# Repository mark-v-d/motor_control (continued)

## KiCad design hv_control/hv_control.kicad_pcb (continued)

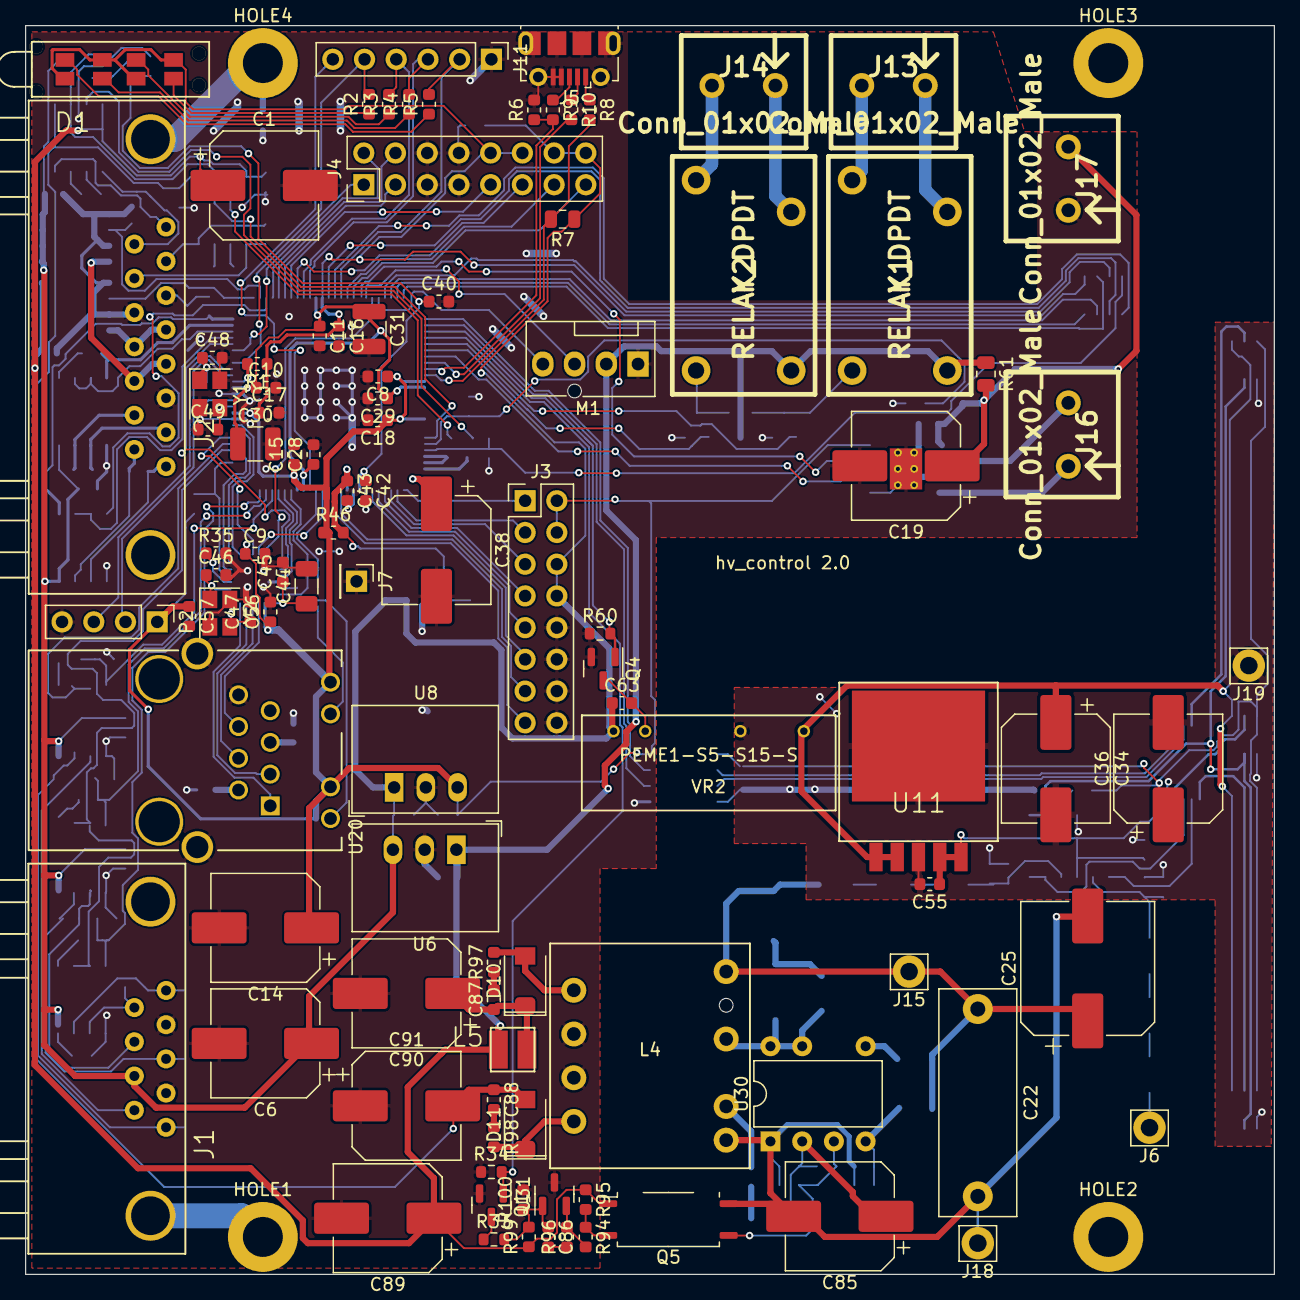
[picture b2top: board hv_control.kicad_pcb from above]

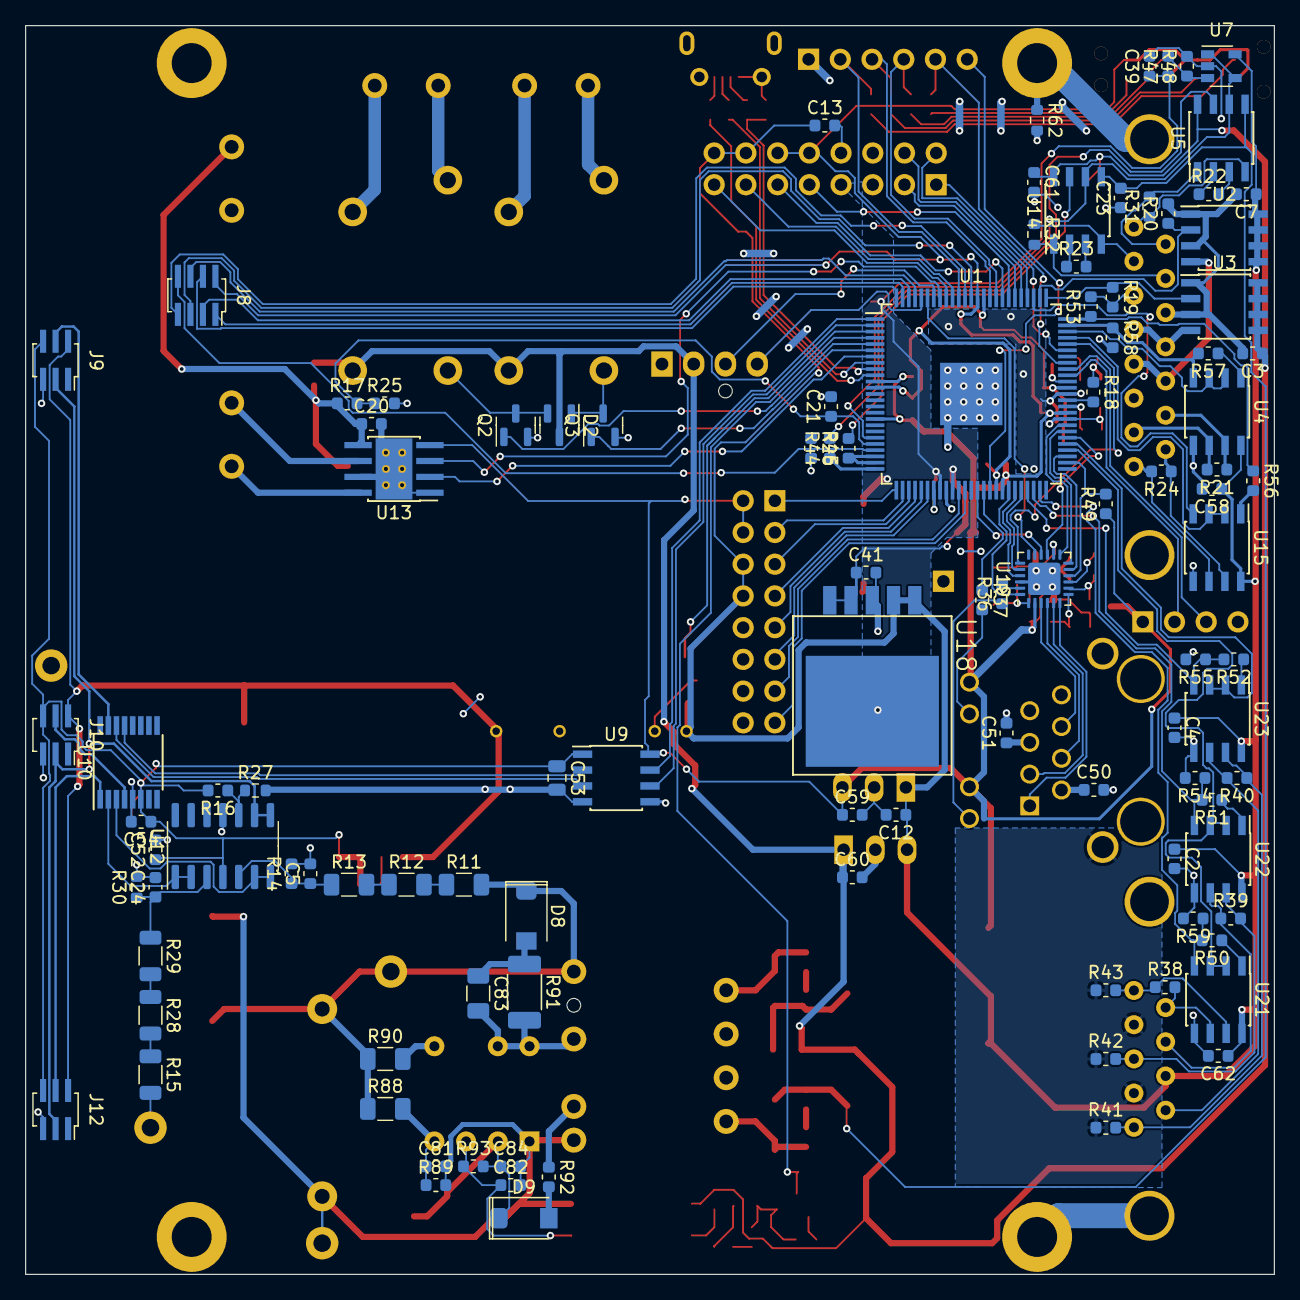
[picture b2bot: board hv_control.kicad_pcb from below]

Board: 2 copper layers, 100.0 x 100.0 mm, 209 parts (105 on the bottom side), 180 nets.

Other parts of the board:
C25: 4.7uF; CP_Elec_10x14.3
Q5: TCLT1003; SOP-4_3.8x7.5mm_P2.54mm

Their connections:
+800V: C25.1; also elsewhere on the board
GNDPWR: C25.2, Q5.4 (E); also elsewhere on the board

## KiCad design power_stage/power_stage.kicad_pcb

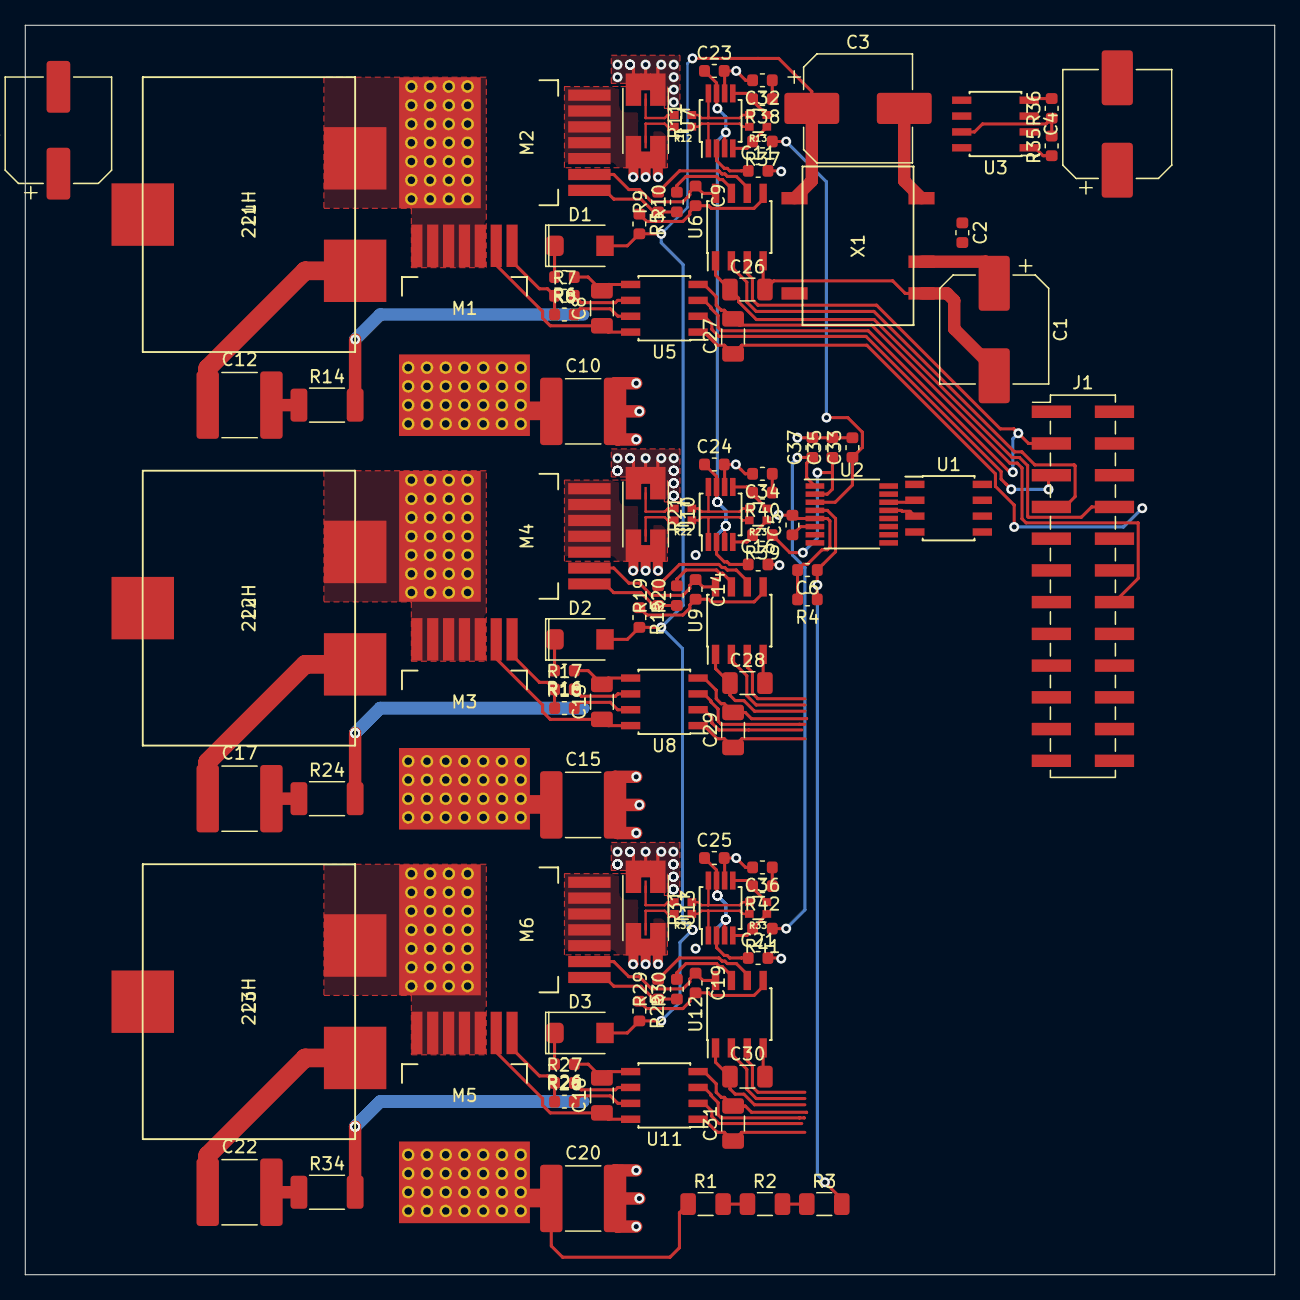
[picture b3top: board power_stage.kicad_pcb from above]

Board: 2 copper layers, 100.0 x 100.0 mm, 105 parts (0 on the bottom side), 94 nets.

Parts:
C1, C3, C4: 100uF/35V; CP_Elec_8x10.5
C2, C5, C6, C11, C16, C21, C23, C24, C25: 100nF; C_0603_1608Metric
C7: 4.7uF/400V; CP_Elec_8x11.9
C8, C13, C18, C26, C27, C28, C29, C30, C31: 1uF; C_1206_3216Metric
C9, C14, C19: 1uF; C_0603_1608Metric
C10, C15, C20: 100nF; C_2220_5650Metric
C12, C17, C22: 1nF; C_2220_5650Metric
C32, C33, C34, C35, C36, C37: 1nF; C_0603_1608Metric
D1, D2, D3: STTH112; D_SMA
J1: Conn_02x12_Odd_Even; PinHeader_2x12_P2.54mm_Vertical_SMD
L1, L2, L3: 22uH; WE-HCF2013
M1, M2, M3, M4, M5, M6: C3M0280090J; TO-263-7-GDSKS
R1, R2, R3: 330k; R_1206_3216Metric
R4: 2.4k; R_0603_1608Metric
R5, R6, R7, R8, R9, R10, R15, R16, R17, R18, R19, R20, R25, R26, R27, R28, R29, R30: 4.7; R_0603_1608Metric
R11, R21, R31: R_Shunt; R_2512_Shunt_Rohm_PMR100_3.0m
R12, R22, R32: 100; ACASN
R13, R23, R33: 2k; ACASN
R14, R24, R34: R; R_2010_5025Metric
R35, R36: R; R_0603_1608Metric
R37, R38, R39, R40, R41, R42: 22; C_0603_1608Metric
U1: ISO7321C; SOIC-8_3.9x4.9mm_P1.27mm
U2: XMC1301T016F0032ABXUMA1; TSSOP-16_4.4x5mm_P0.65mm
U3: LP2951; SOIC-8_3.9x4.9mm_P1.27mm
U5, U6, U8, U9, U11, U12: 1EDI20N12AF; SOIC-8_3.9x4.9mm_P1.27mm
U7, U10, U13: THS4531; MSOP-8_3x3mm_P0.65mm
X1: PDS1-S5-S15-M-TR; CUI_PDS1

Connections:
+3.3V: C26.1, C27.1, C28.1, C29.1, C30.1, C31.1, J1.2, J1.4, J1.6, J1.8, J1.10, J1.12, U1.8, U5.1, U6.1, U8.1, U9.1, U11.1, U12.1
+3.3VP: C4.1, C5.1, C23.1, C24.1, C25.1, R35.1, U1.1, U2.6, U3.1, U7.3, U7.7, U10.3, U10.7, U13.3, U13.7
+15V_prim: C3.1, D1.A, D2.A, D3.A, R5.2, R15.2, R25.2, U3.8, X1.5
+VDC: C7.1, C10.1, C15.1, C20.1, M1.D, M3.D, M5.D, R1.1
/HB0/CURRENT_N: C32.1, R38.1
/HB0/CURRENT_P: C33.1, R37.1, U2.3
/HB0/DISABLE: J1.3, U5.3, U6.3, U8.3, U9.3, U11.3, U12.3
/HB0/H: J1.5, U5.2
/HB0/L: J1.7, U6.2
/HB0/OUT: C12.1, L1.1
/HB0/R_N: R11.3, R12.3
/HB0/R_P: R11.2, R12.4
/HB0/Z_N: R12.2, R13.3, U7.8
/HB0/Z_P: R12.1, R13.4, U7.1
/HB0/cs: M2.S, R11.1
/HB0/sw: L1.2, M1.S, M2.D
/HB1/CURRENT_N: C34.1, R40.1
/HB1/CURRENT_P: C35.1, R39.1, U2.2
/HB1/H: J1.9, U8.2
/HB1/L: J1.11, U9.2
/HB1/OUT: C17.1, L2.1
/HB1/R_N: R21.3, R22.3
/HB1/R_P: R21.2, R22.4
/HB1/Z_N: R22.2, R23.3, U10.8
/HB1/Z_P: R22.1, R23.4, U10.1
/HB1/cs: M4.S, R21.1
/HB1/sw: L2.2, M3.S, M4.D
/HB2/CURRENT_N: C36.1, R42.1
/HB2/CURRENT_P: C37.1, R41.1, U2.1
/HB2/H: J1.13, U11.2
/HB2/L: J1.15, U12.2
/HB2/OUT: C22.1, L3.1
/HB2/R_N: R31.3, R32.3
/HB2/R_P: R31.2, R32.4
/HB2/Z_N: R32.2, R33.3, U13.8
/HB2/Z_P: R32.1, R33.4, U13.1
/HB2/cs: M6.S, R31.1
/HB2/sw: L3.2, M5.S, M6.D
/RXD: U1.3, U2.13
/TXD: U1.2, U2.14
GND: C1.2, C2.2, C26.2, C27.2, C28.2, C29.2, C30.2, C31.2, J1.14, J1.16, J1.18, J1.20, J1.22, J1.24, U1.5, U5.4, U6.4, U8.4, U9.4, U11.4, U12.4, X1.1
GNDPWR: C3.2, C4.2, C5.2, C6.2, C7.2, C10.2, C11.2, C15.2, C16.2, C20.2, C21.2, C23.2, C24.2, C25.2, C32.2, C33.2, C34.2, C35.2, C36.2, C37.2, R4.2, R11.4, R14.2, R21.4, R24.2, R31.4, R34.2, R36.2, U1.4, U2.5, U3.4, U7.6, U10.6, U13.6, X1.4
unnamed: C1.1, C2.1, J1.17, X1.2
unnamed: C6.1, R3.2, R4.1, U2.4
unnamed: C8.1, M1.KS, U5.8
unnamed: C8.2, R6.1, U5.5
unnamed: C9.1, M2.KS, U6.8
unnamed: C9.2, R5.1, U6.5
unnamed: C11.1, U7.2
unnamed: C12.2, R14.1
unnamed: C13.1, M3.KS, U8.8
unnamed: C13.2, R16.1, U8.5
unnamed: C14.1, M4.KS, U9.8
unnamed: C14.2, R15.1, U9.5
unnamed: C16.1, U10.2
unnamed: C17.2, R24.1
unnamed: C18.1, M5.KS, U11.8
unnamed: C18.2, R26.1, U11.5
unnamed: C19.1, M6.KS, U12.8
unnamed: C19.2, R25.1, U12.5
unnamed: C21.1, U13.2
unnamed: C22.2, R34.1
unnamed: D1.C, R6.2
unnamed: D2.C, R16.2
unnamed: D3.C, R26.2
unnamed: J1.19, U1.7
unnamed: J1.21, U1.6
unnamed: M1.G, R7.1, R8.1
unnamed: M2.G, R9.1, R10.1
unnamed: M3.G, R17.1, R18.1
unnamed: M4.G, R19.1, R20.1
unnamed: M5.G, R27.1, R28.1
unnamed: M6.G, R29.1, R30.1
unnamed: R1.2, R2.1
unnamed: R2.2, R3.1
unnamed: R7.2, U5.6
unnamed: R8.2, U5.7
unnamed: R9.2, U6.6
unnamed: R10.2, U6.7
unnamed: R13.1, R37.2, U7.4
unnamed: R13.2, R38.2, U7.5
unnamed: R17.2, U8.6
unnamed: R18.2, U8.7
unnamed: R19.2, U9.6
unnamed: R20.2, U9.7
unnamed: R23.1, R39.2, U10.4
unnamed: R23.2, R40.2, U10.5
unnamed: R27.2, U11.6
unnamed: R28.2, U11.7
unnamed: R29.2, U12.6
unnamed: R30.2, U12.7
unnamed: R33.1, R41.2, U13.4
unnamed: R33.2, R42.2, U13.5
unnamed: R35.2, R36.1, U3.7

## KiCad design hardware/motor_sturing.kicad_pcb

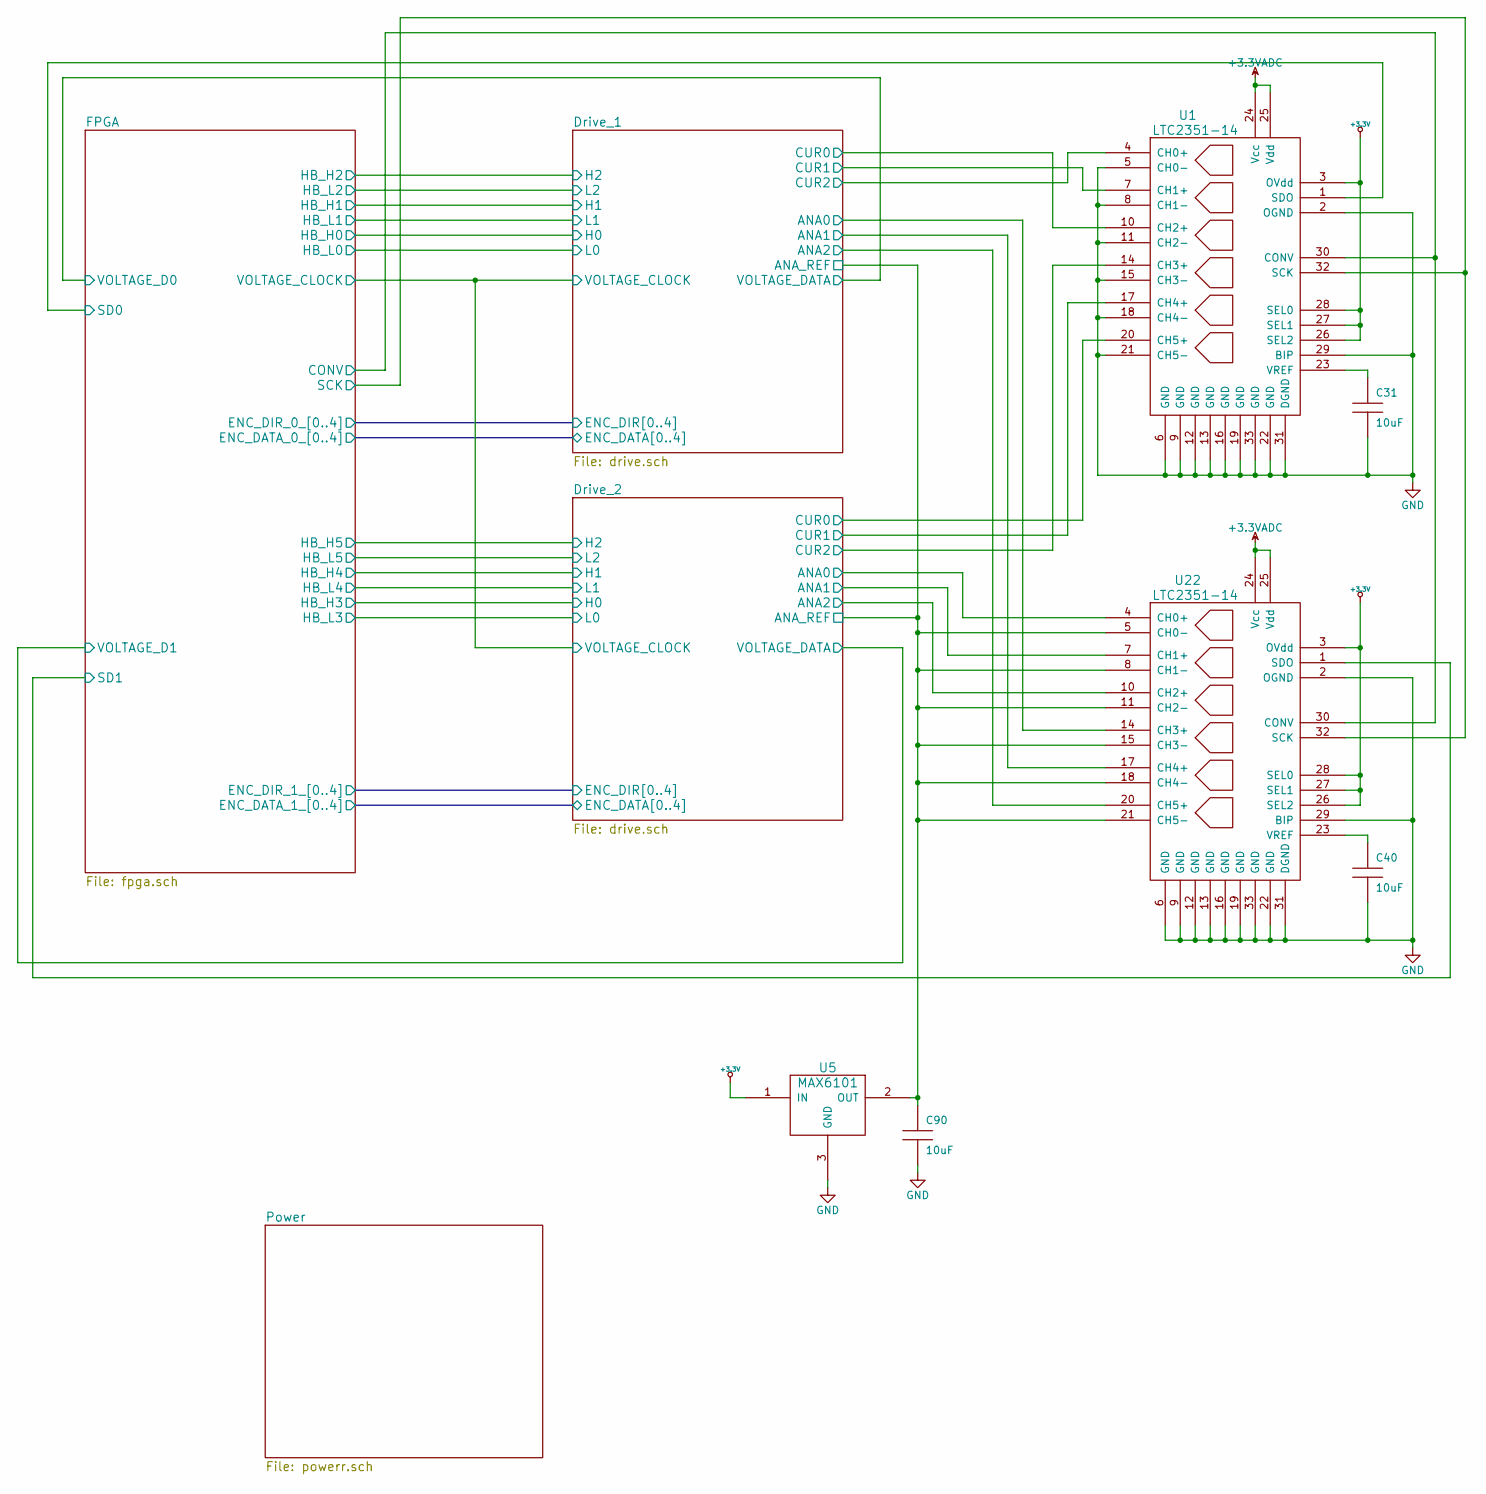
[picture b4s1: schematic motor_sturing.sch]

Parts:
C31, C40, C90: 10uF; C1210
U1, U22: LTC2351-14; QFN-32-1EP_5x5mm_Pitch0.5mm; PartNr LTC2351CUH-14#PBF; Farnell 2294615
U5: MAX6101; SOT-23; digikey MAX6101EUR+TCT-ND

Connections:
+3.3V: U1.3 (OVdd), U1.26 (SEL2), U1.27 (SEL1), U1.28 (SEL0), U5.1 (IN), U22.3 (OVdd), U22.26 (SEL2), U22.27 (SEL1), U22.28 (SEL0); also elsewhere on the board
+3.3VADC: U1.24 (Vcc), U1.25 (Vdd), U22.24 (Vcc), U22.25 (Vdd); also elsewhere on the board
/Drive_1/ANA0: U22.14 (CH3+); also elsewhere on the board
/Drive_1/ANA1: U22.17 (CH4+); also elsewhere on the board
/Drive_1/ANA2: U22.20 (CH5+); also elsewhere on the board
/Drive_1/ANA_REF: C90.1, U5.2 (OUT), U22.5 (CH0-), U22.8 (CH1-), U22.11 (CH2-), U22.15 (CH3-), U22.18 (CH4-), U22.21 (CH5-); also elsewhere on the board
/Drive_1/CUR0: U1.10 (CH2+); also elsewhere on the board
/Drive_1/CUR1: U1.7 (CH1+); also elsewhere on the board
/Drive_1/CUR2: U1.4 (CH0+); also elsewhere on the board
/Drive_2/ANA0: U22.4 (CH0+); also elsewhere on the board
/Drive_2/ANA1: U22.7 (CH1+); also elsewhere on the board
/Drive_2/ANA2: U22.10 (CH2+); also elsewhere on the board
/Drive_2/CUR0: U1.20 (CH5+); also elsewhere on the board
/Drive_2/CUR1: U1.17 (CH4+); also elsewhere on the board
/Drive_2/CUR2: U1.14 (CH3+); also elsewhere on the board
/FPGA/CONV: U1.30 (CONV), U22.30 (CONV); also elsewhere on the board
/FPGA/SCK: U1.32 (SCK), U22.32 (SCK); also elsewhere on the board
/FPGA/SD0: U1.1 (SDO); also elsewhere on the board
/FPGA/SD1: U22.1 (SDO); also elsewhere on the board
GND: C31.2, C40.2, C90.2, U1.2 (OGND), U1.5 (CH0-), U1.6 (GND), U1.8 (CH1-), U1.9 (GND), U1.11 (CH2-), U1.12 (GND), U1.13 (GND), U1.15 (CH3-), U1.16 (GND), U1.18 (CH4-), U1.19 (GND), U1.21 (CH5-), U1.22 (GND), U1.29 (BIP), U1.31 (DGND), U1.33 (GND), U5.3 (GND), U22.2 (OGND), U22.6 (GND), U22.9 (GND), U22.12 (GND), U22.13 (GND), U22.16 (GND), U22.19 (GND), U22.22 (GND), U22.29 (BIP), U22.31 (DGND), U22.33 (GND); also elsewhere on the board
unnamed: C31.1, U1.23 (VREF)
unnamed: C40.1, U22.23 (VREF)
